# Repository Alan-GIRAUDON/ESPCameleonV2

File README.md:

# ESPCameleonV2

# Summary of the project

ESPCameleonV2 is an ESP32 Camera PCB. It resolve the biggest issues of its first version, [ESP32Cameleon](https://github.com/Alan-GIRAUDON/ESPCameleon). This board allow video capture and streaming through WiFi or USB.

## Schematics

## Features

- Micro-USB connector to directly program and power the board
- LDO converters, 3V3 for the ESP32, SD card and LED's, 1V2 and 2V8 for the camera
- RESET plated hole to reset the ESP32 and BOOT plated hole to activate the ESP32 USB boot mode
- FPC connector 24 pins for the camera (tested OV2640, should support OV5640 despite voltage difference)
- Micro-SD card reader to store videos
- White and yellow LED's for debugging and status indicating, red power LED
- Pin header to expose the ESP32 UART interface, the 3V3 rails and GND
- External 8MB PSRAM

## Differences with ESPCameleon

- Added external PSRAM, from 4MB internal PSRAM to 8MB external PSRAM
- Remapped the camera pins to increase the number of parallel lines from 7 to 9
- Removed the additional GPIOS on the header to gain space
- Remapped the SD card to not interfere with the PSRAM
- Replaced the BOOT and RESET button with plated holes to save space
- Removed 1 mounting hole to save space
- Reduced the board size to put the antenna out of the board
- Reorganized traces and components to fit the reduced area
- Updated the silkscreen
## PCB caracteristics

The PCB is a two layer board with single-sided assembly, the thinnest trace is 0.1562 mm and the vias have a 0.7 mm diameter ring and a 0.3 mm hole. The USB traces are as short and as thick as possible to be as close as possible to the 90 $\Omega$ impedance of the JLCPCB two-layer board stackup.

## Board results :

Currently, the board hasn't been produced and rested.

## Programming

The board can be "easily" programmed with both ESP-IDF and Arduino IDE but the later is much faster to get working.

For the arduino IDE, you just need to download the ESP32 boards configurations. Select board "ESP32S2 Dev module", enable "USB CDC on boot", "upload mode" as "internal USB". For the camera webserver example (File->Example->ESP32->Camera->CameraWebServer), you should set "PSRAM" as "enabled", enter your Wifi credentials and update the camera_pins.h to match the board (an example is given in my CameraWebServer2 repository).

An example of streaming through the USB port is available in the USBCameraStreaming repository. It contains an Arduino script to send JPEG images via USB and a Basic Flutter android app to receive and display the video stream.

## Current Issues and TO DO list

- The board needs to be tested to identify possibles issues
- By default, ESP32S2 modules uses SPI pins that aren't exposed to link the PSRAM, whether it is functional with other pins remain to be tested.

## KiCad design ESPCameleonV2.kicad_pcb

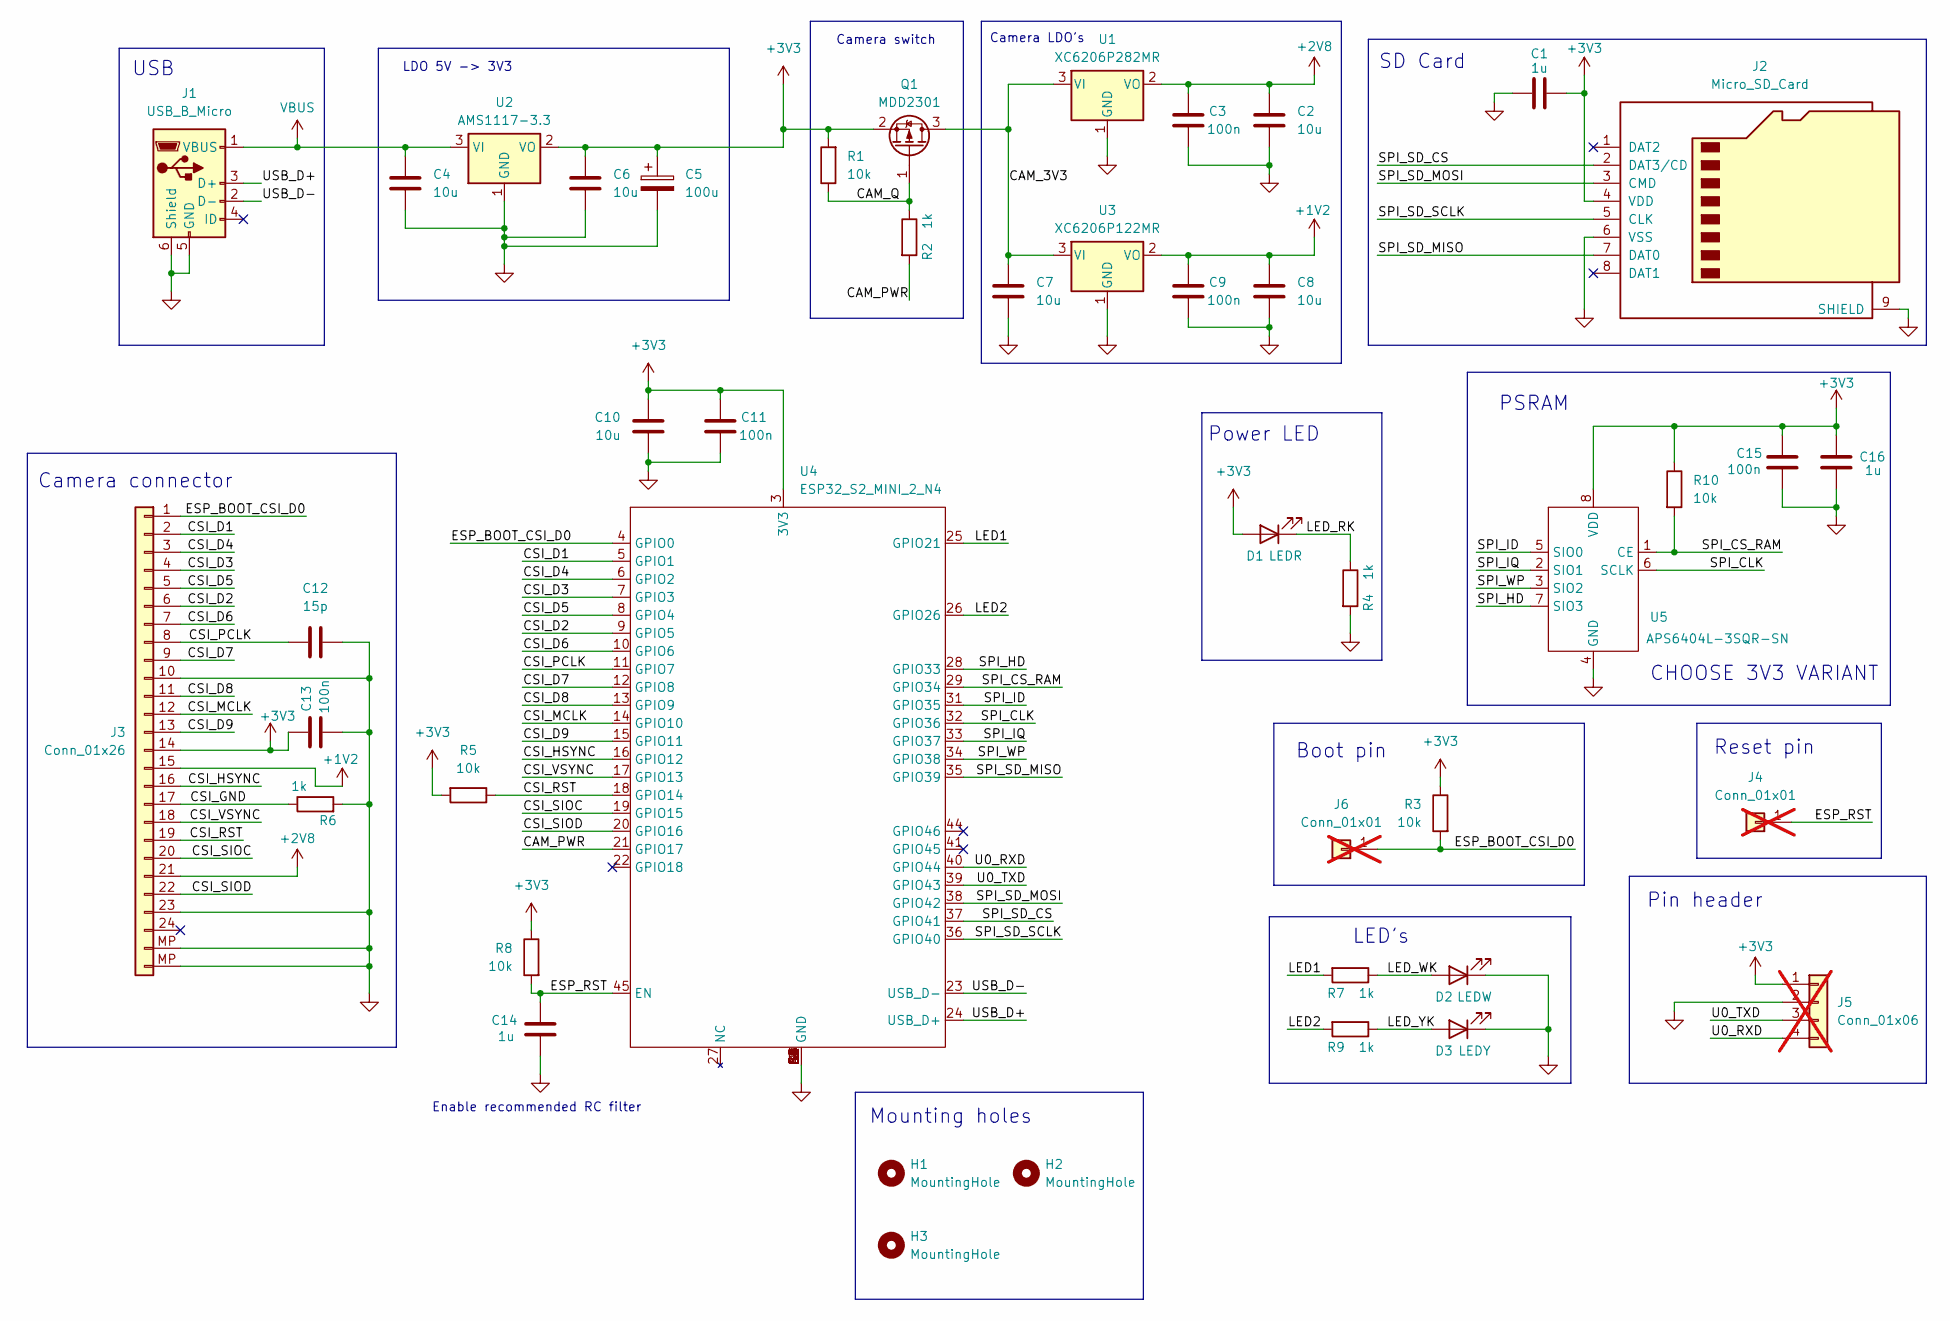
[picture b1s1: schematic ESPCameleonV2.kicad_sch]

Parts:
C1, C14, C16: 1u; C_0603_1608Metric; LCSC Part # C15849
C2, C4, C6, C7, C8, C10: 10u; C_0402_1005Metric; LCSC Part # C15525
C3, C9, C11, C13, C15: 100n; C_0402_1005Metric; LCSC Part # C307331
C5: 100u; CP_EIA-3528-21_Kemet-B; LCSC Part # C16133
C12: 15p; C_0402_1005Metric; LCSC Part # C1548
D1: LEDR; LED_0603_1608Metric; LCSC Part # C2286
D2: LEDW; LED_0603_1608Metric; LCSC Part # C2290
D3: LEDY; LED_0603_1608Metric; LCSC Part # C72038
H1, H2, H3: MountingHole; MountingHole_2.2mm_M2_ISO7380; LCSC Part # X
J1: USB_B_Micro; USB_Micro-B_XKB_U254-051T-4BH83-F1S; LCSC Part # C393940
J2: Micro_SD_Card; GCT_MEM2075-00-140-01-A; LCSC Part # C393941
J3: Conn_01x26; AFC01_S24FCA_00; LCSC Part # C262669
J4, J6: Conn_01x01; PinHeader_1x01_P1.00mm_Vertical; not fitted
J5: Conn_01x06; PinHeader_1x04_P2.54mm_Vertical; LCSC Part # C6332199; not fitted
Q1: MDD2301; SOT-23; LCSC Part # C427391
R1, R3, R5, R8, R10: 10k; R_0402_1005Metric; LCSC Part # C25744
R2, R4, R6, R7, R9: 1k; R_0402_1005Metric; LCSC Part # C11702
U1: XC6206P282MR; SOT-23-3; LCSC Part # C5148690
U2: AMS1117-3.3; SOT-223-3_TabPin2; LCSC Part # C6186
U3: XC6206P122MR; SOT-23-3; LCSC Part # C2827649
U4: ESP32_S2_MINI_2_N4; ESP32-S2-MINI-2; LCSC Part # C3013906
U5: APS6404L-3SQR-SN; SOP-8_3.9x4.9mm_P1.27mm; LCSC Part # C5333729

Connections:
+1V2: C8.1, C9.2, J3.15, U3.2 (VO)
+2V8: C2.1, C3.2, J3.21, U1.2 (VO)
+3V3: C1.2, C5.1, C6.1, C10.1, C11.2, C13.2, C15.2, C16.2, D1.2 (A), J2.4 (VDD), J3.14, J5.1, Q1.2 (S), R1.2, R3.1, R5.2, R8.1, R10.1, U2.2 (VO), U4.3 (3V3), U5.8 (VDD)
/CAM_3V3: C7.1, Q1.3 (D), U1.3 (VI), U3.3 (VI)
/CAM_PWR: R2.2, U4.21 (GPIO17)
/CAM_Q: Q1.1 (G), R1.1, R2.1
/CSI_D1: J3.2, U4.5 (GPIO1)
/CSI_D2: J3.6, U4.9 (GPIO5)
/CSI_D3: J3.4, U4.7 (GPIO3)
/CSI_D4: J3.3, U4.6 (GPIO2)
/CSI_D5: J3.5, U4.8 (GPIO4)
/CSI_D6: J3.7, U4.10 (GPIO6)
/CSI_D7: J3.9, U4.12 (GPIO8)
/CSI_D8: J3.11, U4.13 (GPIO9)
/CSI_D9: J3.13, U4.15 (GPIO11)
/CSI_GND: J3.17, R6.1
/CSI_HSYNC: J3.16, U4.16 (GPIO12)
/CSI_MCLK: J3.12, U4.14 (GPIO10)
/CSI_PCLK: C12.1, J3.8, U4.11 (GPIO7)
/CSI_RST: J3.19, R5.1, U4.18 (GPIO14)
/CSI_SIOC: J3.20, U4.19 (GPIO15)
/CSI_SIOD: J3.22, U4.20 (GPIO16)
/CSI_VSYNC: J3.18, U4.17 (GPIO13)
/ESP_BOOT_CSI_D0: J3.1, J6.1, R3.2, U4.4 (GPIO0)
/ESP_RST: C14.1, J4.1, R8.2, U4.45 (EN)
/LED1: R7.2, U4.25 (GPIO21)
/LED2: R9.2, U4.26 (GPIO26)
/LED_RK: D1.1 (K), R4.1
/LED_WK: D2.2 (A), R7.1
/LED_YK: D3.2 (A), R9.1
/SPI_CLK: U4.32 (GPIO36), U5.6 (SCLK)
/SPI_CS_RAM: R10.2, U4.29 (GPIO34), U5.1 (CE)
/SPI_HD: U4.28 (GPIO33), U5.7 (SIO3)
/SPI_ID: U4.31 (GPIO35), U5.5 (SIO0)
/SPI_IQ: U4.33 (GPIO37), U5.2 (SIO1)
/SPI_SD_CS: J2.2 (DAT3/CD), U4.37 (GPIO41)
/SPI_SD_MISO: J2.7 (DAT0), U4.35 (GPIO39)
/SPI_SD_MOSI: J2.3 (CMD), U4.38 (GPIO42)
/SPI_SD_SCLK: J2.5 (CLK), U4.36 (GPIO40)
/SPI_WP: U4.34 (GPIO38), U5.3 (SIO2)
/U0_RXD: J5.4, U4.40 (GPIO44)
/U0_TXD: J5.3, U4.39 (GPIO43)
/USB_D+: J1.3 (D+), U4.24 (USB_D+)
/USB_D-: J1.2 (D-), U4.23 (USB_D-)
GND: C1.1, C2.2, C3.1, C4.2, C5.2, C6.2, C7.2, C8.2, C9.1, C10.2, C11.1, C12.2, C13.1, C14.2, C15.1, C16.1, D2.1 (K), D3.1 (K), J1.5 (GND), J1.6 (Shield), J2.6 (VSS), J2.9 (SHIELD), J3.10, J3.23, J3.MP, J5.2, R4.2, R6.2, U1.1 (GND), U2.1 (GND), U3.1 (GND), U4.1 (GND), U4.2 (GND), U4.30 (GND), U4.42 (GND), U4.43 (GND), U4.46 (GND), U4.47 (GND), U4.48 (GND), U4.49 (GND), U4.50 (GND), U4.51 (GND), U4.52 (GND), U4.53 (GND), U4.54 (GND), U4.55 (GND), U4.56 (GND), U4.57 (GND), U4.58 (GND), U4.59 (GND), U4.60 (GND), U4.61 (GND), U4.62 (GND), U4.63 (GND), U4.64 (GND), U4.65 (GND), U5.4 (GND)
VBUS: C4.1, J1.1 (VBUS), U2.3 (VI)

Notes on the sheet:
SD Card
USB
CHOOSE 3V3 VARIANT
Reset pin
Enable recommended RC filter
PSRAM
Camera switch
Mounting holes
Boot pin
LED's
Pin header
LDO 5V -> 3V3
Camera connector
Power LED
Camera LDO's

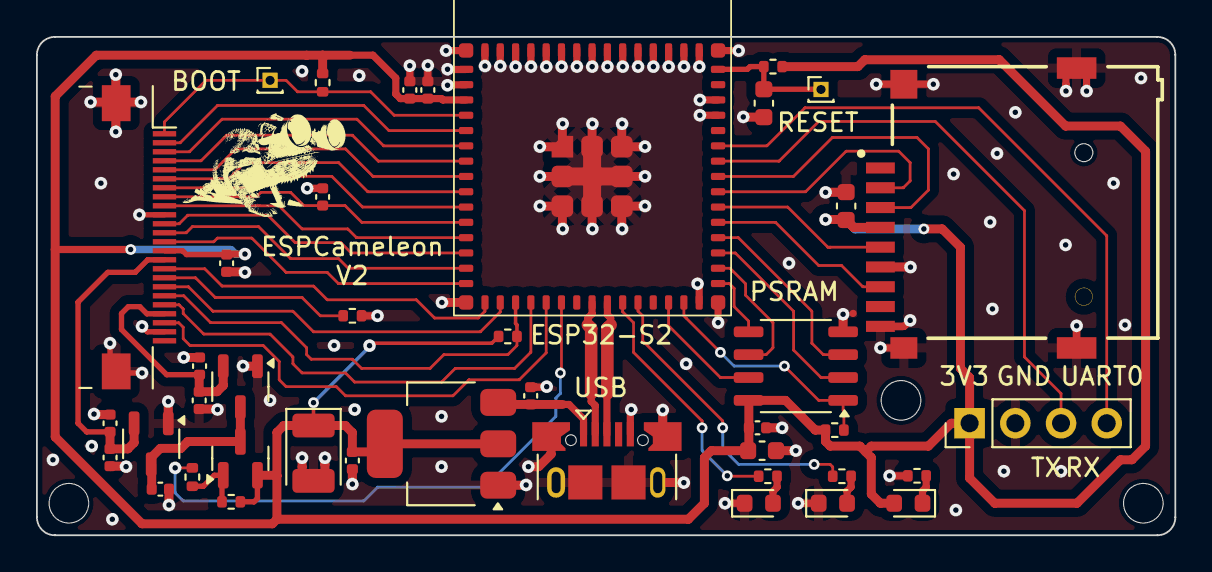
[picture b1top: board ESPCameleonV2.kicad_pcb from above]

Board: 2 copper layers, 63.2 x 27.7 mm, 44 parts (0 on the bottom side), 46 nets.

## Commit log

2024-12-04 Create LICENSE
